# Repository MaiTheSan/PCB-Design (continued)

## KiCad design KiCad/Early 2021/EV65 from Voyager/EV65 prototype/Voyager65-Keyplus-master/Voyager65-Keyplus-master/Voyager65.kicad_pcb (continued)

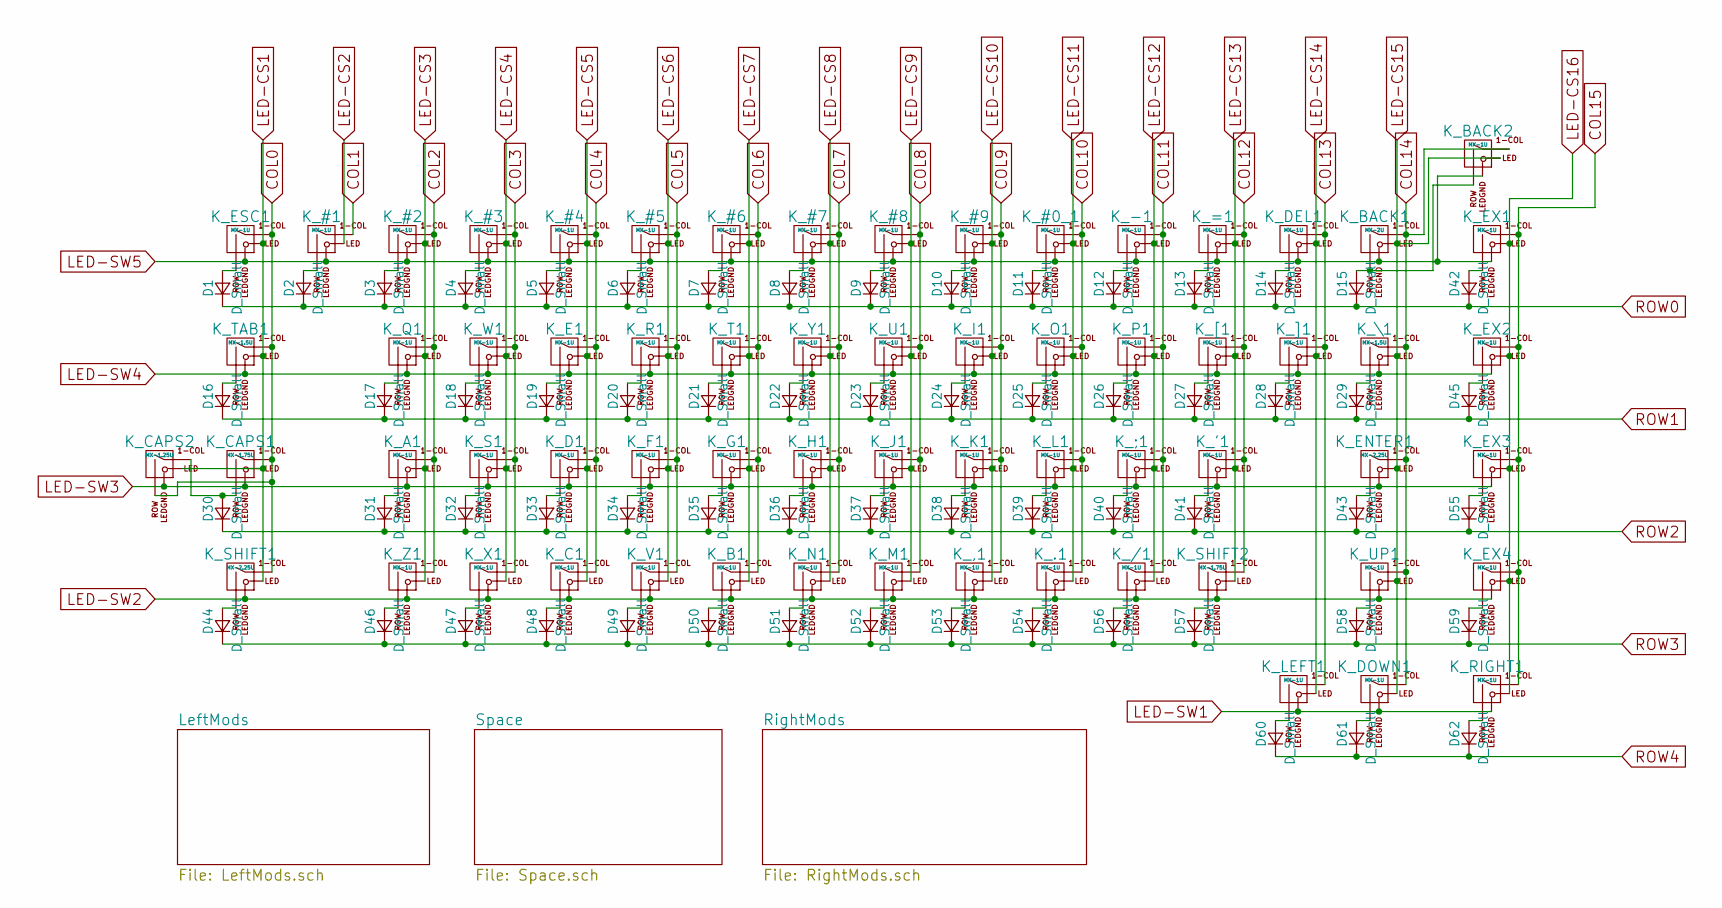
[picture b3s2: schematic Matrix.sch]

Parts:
D1, D2, D3, D4, D5, D6, D7, D8, D9, D10, D11, D12, D13, D14, D15, D16, D17, D18, D19, D20, D21, D22, D23, D24, D25, D26, D27, D28, D29, D30, D31, D32, D33, D34, D35, D36, D37, D38, D39, D40, D41, D42, D43, D44, D45, D46, D47, D48, D49, D50, D51, D52, D53, D54, D55, D56, D57, D58, D59, D60, D61, D62: D_Small; D_SOD-123
K_#0_1, K_#1, K_#2, K_#3, K_#4, K_#5, K_#6, K_#7, K_#8, K_#9: MX-1U; MXOnly-1U
K_'1: MX-1U; MXOnly-1U
K_,1: MX-1U; MXOnly-1U
K_-1: MX-1U; MXOnly-1U
K_.1: MX-1U; MXOnly-1U
K_/1: MX-1U; MXOnly-1U
K_;1: MX-1U; MXOnly-1U
K_=1: MX-1U; MXOnly-1U
K_A1: MX-1U; MXOnly-1U
K_B1: MX-1U; MXOnly-1U
K_BACK1: MX-2U; MXOnly-2U
K_BACK2: MX-1U; MXOnly-1U
K_C1: MX-1U; MXOnly-1U
K_CAPS1: MX-1.75U; MXOnly-1.75U
K_CAPS2: MX-1.25U; MXOnly-1.25U-FLIPPED
K_D1: MX-1U; MXOnly-1U
K_DEL1: MX-1U; MXOnly-1U
K_DOWN1: MX-1U; MXOnly-1U
K_E1: MX-1U; MXOnly-1U
K_ENTER1: MX-2.25U; MXOnly-2.25U
K_ESC1: MX-1U; MXOnly-1U
K_EX1, K_EX2, K_EX3, K_EX4: MX-1U; MXOnly-1U
K_F1: MX-1U; MXOnly-1U
K_G1: MX-1U; MXOnly-1U
K_H1: MX-1U; MXOnly-1U
K_I1: MX-1U; MXOnly-1U
K_J1: MX-1U; MXOnly-1U
K_K1: MX-1U; MXOnly-1U
K_L1: MX-1U; MXOnly-1U
K_LEFT1: MX-1U; MXOnly-1U
K_M1: MX-1U; MXOnly-1U
K_N1: MX-1U; MXOnly-1U
K_O1: MX-1U; MXOnly-1U
K_P1: MX-1U; MXOnly-1U
K_Q1: MX-1U; MXOnly-1U
K_R1: MX-1U; MXOnly-1U
K_RIGHT1: MX-1U; MXOnly-1U
K_S1: MX-1U; MXOnly-1U
K_SHIFT1: MX-2.25U; MXOnly-2.25U
K_SHIFT2: MX-1.75U; MXOnly-1.75U
K_T1: MX-1U; MXOnly-1U
K_TAB1: MX-1.5U; MXOnly-1.5U
K_U1: MX-1U; MXOnly-1U
K_UP1: MX-1U; MXOnly-1U
K_V1: MX-1U; MXOnly-1U
K_W1: MX-1U; MXOnly-1U
K_X1: MX-1U; MXOnly-1U
K_Y1: MX-1U; MXOnly-1U
K_Z1: MX-1U; MXOnly-1U
K_[1: MX-1U; MXOnly-1U
K_\1: MX-1.5U; MXOnly-1.5U
K_]1: MX-1U; MXOnly-1U

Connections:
COL0: K_CAPS1.1 (COL), K_CAPS2.2 (ROW), K_ESC1.1 (COL), K_SHIFT1.1 (COL), K_TAB1.1 (COL); also elsewhere on the board
COL1: K_#1.1 (COL); also elsewhere on the board
COL2: K_#2.1 (COL), K_A1.1 (COL), K_Q1.1 (COL), K_Z1.1 (COL); also elsewhere on the board
COL3: K_#3.1 (COL), K_S1.1 (COL), K_W1.1 (COL), K_X1.1 (COL); also elsewhere on the board
COL4: K_#4.1 (COL), K_C1.1 (COL), K_D1.1 (COL), K_E1.1 (COL); also elsewhere on the board
COL5: K_#5.1 (COL), K_F1.1 (COL), K_R1.1 (COL), K_V1.1 (COL); also elsewhere on the board
COL6: K_#6.1 (COL), K_B1.1 (COL), K_G1.1 (COL), K_T1.1 (COL); also elsewhere on the board
COL7: K_#7.1 (COL), K_H1.1 (COL), K_N1.1 (COL), K_Y1.1 (COL); also elsewhere on the board
COL8: K_#8.1 (COL), K_J1.1 (COL), K_M1.1 (COL), K_U1.1 (COL); also elsewhere on the board
COL9: K_#9.1 (COL), K_,1.1 (COL), K_I1.1 (COL), K_K1.1 (COL); also elsewhere on the board
COL10: K_#0_1.1 (COL), K_.1.1 (COL), K_L1.1 (COL), K_O1.1 (COL); also elsewhere on the board
COL11: K_-1.1 (COL), K_/1.1 (COL), K_;1.1 (COL), K_P1.1 (COL); also elsewhere on the board
COL12: K_'1.1 (COL), K_=1.1 (COL), K_SHIFT2.1 (COL), K_[1.1 (COL); also elsewhere on the board
COL13: K_DEL1.1 (COL), K_LEFT1.1 (COL), K_]1.1 (COL); also elsewhere on the board
COL14: K_BACK1.1 (COL), K_BACK2.1 (COL), K_DOWN1.1 (COL), K_ENTER1.1 (COL), K_UP1.1 (COL), K_\1.1 (COL); also elsewhere on the board
COL15: K_EX1.1 (COL), K_EX2.1 (COL), K_EX3.1 (COL), K_EX4.1 (COL), K_RIGHT1.1 (COL); also elsewhere on the board
LED-CS1: K_CAPS1.3 (LED), K_CAPS2.3 (LED), K_ESC1.3 (LED), K_SHIFT1.3 (LED), K_TAB1.3 (LED); also elsewhere on the board
LED-CS2: K_#1.3 (LED); also elsewhere on the board
LED-CS3: K_#2.3 (LED), K_A1.3 (LED), K_Q1.3 (LED), K_Z1.3 (LED); also elsewhere on the board
LED-CS4: K_#3.3 (LED), K_S1.3 (LED), K_W1.3 (LED), K_X1.3 (LED); also elsewhere on the board
LED-CS5: K_#4.3 (LED), K_C1.3 (LED), K_D1.3 (LED), K_E1.3 (LED); also elsewhere on the board
LED-CS6: K_#5.3 (LED), K_F1.3 (LED), K_R1.3 (LED), K_V1.3 (LED); also elsewhere on the board
LED-CS7: K_#6.3 (LED), K_B1.3 (LED), K_G1.3 (LED), K_T1.3 (LED); also elsewhere on the board
LED-CS8: K_#7.3 (LED), K_H1.3 (LED), K_N1.3 (LED), K_Y1.3 (LED); also elsewhere on the board
LED-CS9: K_#8.3 (LED), K_J1.3 (LED), K_M1.3 (LED), K_U1.3 (LED); also elsewhere on the board
LED-CS10: K_#9.3 (LED), K_,1.3 (LED), K_I1.3 (LED), K_K1.3 (LED); also elsewhere on the board
LED-CS11: K_#0_1.3 (LED), K_.1.3 (LED), K_L1.3 (LED), K_O1.3 (LED); also elsewhere on the board
LED-CS12: K_-1.3 (LED), K_/1.3 (LED), K_;1.3 (LED), K_P1.3 (LED); also elsewhere on the board
LED-CS13: K_'1.3 (LED), K_=1.3 (LED), K_SHIFT2.3 (LED), K_[1.3 (LED); also elsewhere on the board
LED-CS14: K_DEL1.3 (LED), K_LEFT1.3 (LED), K_]1.3 (LED); also elsewhere on the board
LED-CS15: K_BACK1.3 (LED), K_BACK2.3 (LED), K_DOWN1.3 (LED), K_ENTER1.3 (LED), K_UP1.3 (LED), K_\1.3 (LED); also elsewhere on the board
LED-CS16: K_EX1.3 (LED), K_EX2.3 (LED), K_EX3.3 (LED), K_EX4.3 (LED), K_RIGHT1.3 (LED); also elsewhere on the board
LED-SW1: K_DOWN1.4 (LEDGND), K_LEFT1.4 (LEDGND), K_RIGHT1.4 (LEDGND); also elsewhere on the board
LED-SW2: K_,1.4 (LEDGND), K_.1.4 (LEDGND), K_/1.4 (LEDGND), K_B1.4 (LEDGND), K_C1.4 (LEDGND), K_EX4.4 (LEDGND), K_M1.4 (LEDGND), K_N1.4 (LEDGND), K_SHIFT1.4 (LEDGND), K_SHIFT2.4 (LEDGND), K_UP1.4 (LEDGND), K_V1.4 (LEDGND), K_X1.4 (LEDGND), K_Z1.4 (LEDGND); also elsewhere on the board
LED-SW3: K_'1.4 (LEDGND), K_;1.4 (LEDGND), K_A1.4 (LEDGND), K_CAPS1.4 (LEDGND), K_CAPS2.4 (LEDGND), K_D1.4 (LEDGND), K_ENTER1.4 (LEDGND), K_EX3.4 (LEDGND), K_F1.4 (LEDGND), K_G1.4 (LEDGND), K_H1.4 (LEDGND), K_J1.4 (LEDGND), K_K1.4 (LEDGND), K_L1.4 (LEDGND), K_S1.4 (LEDGND); also elsewhere on the board
LED-SW4: K_E1.4 (LEDGND), K_EX2.4 (LEDGND), K_I1.4 (LEDGND), K_O1.4 (LEDGND), K_P1.4 (LEDGND), K_Q1.4 (LEDGND), K_R1.4 (LEDGND), K_T1.4 (LEDGND), K_TAB1.4 (LEDGND), K_U1.4 (LEDGND), K_W1.4 (LEDGND), K_Y1.4 (LEDGND), K_[1.4 (LEDGND), K_\1.4 (LEDGND), K_]1.4 (LEDGND); also elsewhere on the board
LED-SW5: K_#0_1.4 (LEDGND), K_#1.4 (LEDGND), K_#2.4 (LEDGND), K_#3.4 (LEDGND), K_#4.4 (LEDGND), K_#5.4 (LEDGND), K_#6.4 (LEDGND), K_#7.4 (LEDGND), K_#8.4 (LEDGND), K_#9.4 (LEDGND), K_-1.4 (LEDGND), K_=1.4 (LEDGND), K_BACK1.4 (LEDGND), K_BACK2.4 (LEDGND), K_DEL1.4 (LEDGND), K_ESC1.4 (LEDGND), K_EX1.4 (LEDGND); also elsewhere on the board
unnamed: D1.2 (A), K_ESC1.2 (ROW)
unnamed: D2.2 (A), K_#1.2 (ROW)
unnamed: D3.2 (A), K_#2.2 (ROW)
unnamed: D4.2 (A), K_#3.2 (ROW)
unnamed: D5.2 (A), K_#4.2 (ROW)
unnamed: D6.2 (A), K_#5.2 (ROW)
unnamed: D7.2 (A), K_#6.2 (ROW)
unnamed: D8.2 (A), K_#7.2 (ROW)
unnamed: D9.2 (A), K_#8.2 (ROW)
unnamed: D10.2 (A), K_#9.2 (ROW)
unnamed: D11.2 (A), K_#0_1.2 (ROW)
unnamed: D12.2 (A), K_-1.2 (ROW)
unnamed: D13.2 (A), K_=1.2 (ROW)
unnamed: D14.2 (A), K_DEL1.2 (ROW)
unnamed: D15.2 (A), K_BACK1.2 (ROW), K_BACK2.2 (ROW)
unnamed: D16.2 (A), K_TAB1.2 (ROW)
unnamed: D17.2 (A), K_Q1.2 (ROW)
unnamed: D18.2 (A), K_W1.2 (ROW)
unnamed: D19.2 (A), K_E1.2 (ROW)
unnamed: D20.2 (A), K_R1.2 (ROW)
unnamed: D21.2 (A), K_T1.2 (ROW)
unnamed: D22.2 (A), K_Y1.2 (ROW)
unnamed: D23.2 (A), K_U1.2 (ROW)
unnamed: D24.2 (A), K_I1.2 (ROW)
unnamed: D25.2 (A), K_O1.2 (ROW)
unnamed: D26.2 (A), K_P1.2 (ROW)
unnamed: D27.2 (A), K_[1.2 (ROW)
unnamed: D28.2 (A), K_]1.2 (ROW)
unnamed: D29.2 (A), K_\1.2 (ROW)
unnamed: D30.2 (A), K_CAPS1.2 (ROW), K_CAPS2.1 (COL)
unnamed: D31.2 (A), K_A1.2 (ROW)
unnamed: D32.2 (A), K_S1.2 (ROW)
unnamed: D33.2 (A), K_D1.2 (ROW)
unnamed: D34.2 (A), K_F1.2 (ROW)
unnamed: D35.2 (A), K_G1.2 (ROW)
unnamed: D36.2 (A), K_H1.2 (ROW)
unnamed: D37.2 (A), K_J1.2 (ROW)
unnamed: D38.2 (A), K_K1.2 (ROW)
unnamed: D39.2 (A), K_L1.2 (ROW)
unnamed: D40.2 (A), K_;1.2 (ROW)
unnamed: D41.2 (A), K_'1.2 (ROW)
unnamed: D42.2 (A), K_EX1.2 (ROW)
unnamed: D43.2 (A), K_ENTER1.2 (ROW)
unnamed: D44.2 (A), K_SHIFT1.2 (ROW)
unnamed: D45.2 (A), K_EX2.2 (ROW)
unnamed: D46.2 (A), K_Z1.2 (ROW)
unnamed: D47.2 (A), K_X1.2 (ROW)
unnamed: D48.2 (A), K_C1.2 (ROW)
unnamed: D49.2 (A), K_V1.2 (ROW)
unnamed: D50.2 (A), K_B1.2 (ROW)
unnamed: D51.2 (A), K_N1.2 (ROW)
unnamed: D52.2 (A), K_M1.2 (ROW)
unnamed: D53.2 (A), K_,1.2 (ROW)
unnamed: D54.2 (A), K_.1.2 (ROW)
unnamed: D55.2 (A), K_EX3.2 (ROW)
unnamed: D56.2 (A), K_/1.2 (ROW)
unnamed: D57.2 (A), K_SHIFT2.2 (ROW)
unnamed: D58.2 (A), K_UP1.2 (ROW)
unnamed: D59.2 (A), K_EX4.2 (ROW)
unnamed: D60.2 (A), K_LEFT1.2 (ROW)
unnamed: D61.2 (A), K_DOWN1.2 (ROW)
unnamed: D62.2 (A), K_RIGHT1.2 (ROW)
ROW0: D1.1 (K), D2.1 (K), D3.1 (K), D4.1 (K), D5.1 (K), D6.1 (K), D7.1 (K), D8.1 (K), D9.1 (K), D10.1 (K), D11.1 (K), D12.1 (K), D13.1 (K), D14.1 (K), D15.1 (K), D42.1 (K); also elsewhere on the board
ROW1: D16.1 (K), D17.1 (K), D18.1 (K), D19.1 (K), D20.1 (K), D21.1 (K), D22.1 (K), D23.1 (K), D24.1 (K), D25.1 (K), D26.1 (K), D27.1 (K), D28.1 (K), D29.1 (K), D45.1 (K); also elsewhere on the board
ROW2: D30.1 (K), D31.1 (K), D32.1 (K), D33.1 (K), D34.1 (K), D35.1 (K), D36.1 (K), D37.1 (K), D38.1 (K), D39.1 (K), D40.1 (K), D41.1 (K), D43.1 (K), D55.1 (K); also elsewhere on the board
ROW3: D44.1 (K), D46.1 (K), D47.1 (K), D48.1 (K), D49.1 (K), D50.1 (K), D51.1 (K), D52.1 (K), D53.1 (K), D54.1 (K), D56.1 (K), D57.1 (K), D58.1 (K), D59.1 (K); also elsewhere on the board
ROW4: D60.1 (K), D61.1 (K), D62.1 (K); also elsewhere on the board

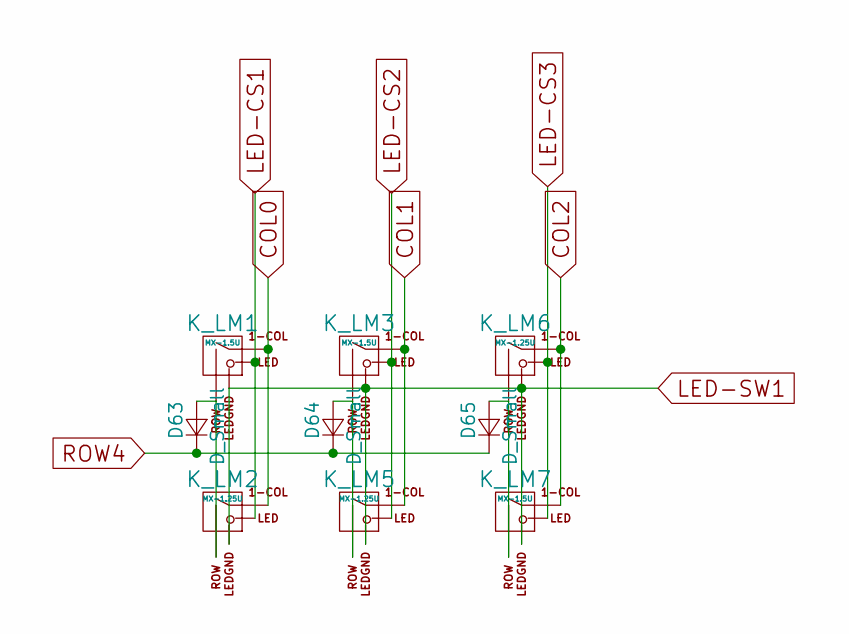
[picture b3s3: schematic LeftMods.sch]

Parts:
D63, D64, D65: D_Small; D_SOD-123
K_LM1, K_LM3, K_LM7: MX-1.5U; MXOnly-1.5U
K_LM2, K_LM5, K_LM6: MX-1.25U; MXOnly-1.25U-FLIPPED

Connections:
COL0: K_LM1.1 (COL), K_LM2.1 (COL); also elsewhere on the board
COL1: K_LM3.1 (COL), K_LM5.1 (COL); also elsewhere on the board
COL2: K_LM6.1 (COL), K_LM7.1 (COL); also elsewhere on the board
LED-CS1: K_LM1.3 (LED), K_LM2.3 (LED); also elsewhere on the board
LED-CS2: K_LM3.3 (LED), K_LM5.3 (LED); also elsewhere on the board
LED-CS3: K_LM6.3 (LED), K_LM7.3 (LED); also elsewhere on the board
LED-SW1: K_LM1.4 (LEDGND), K_LM2.4 (LEDGND), K_LM3.4 (LEDGND), K_LM5.4 (LEDGND), K_LM6.4 (LEDGND), K_LM7.4 (LEDGND); also elsewhere on the board
unnamed: D63.2 (A), K_LM1.2 (ROW), K_LM2.2 (ROW)
unnamed: D64.2 (A), K_LM3.2 (ROW), K_LM5.2 (ROW)
unnamed: D65.2 (A), K_LM6.2 (ROW), K_LM7.2 (ROW)
ROW4: D63.1 (K), D64.1 (K), D65.1 (K); also elsewhere on the board

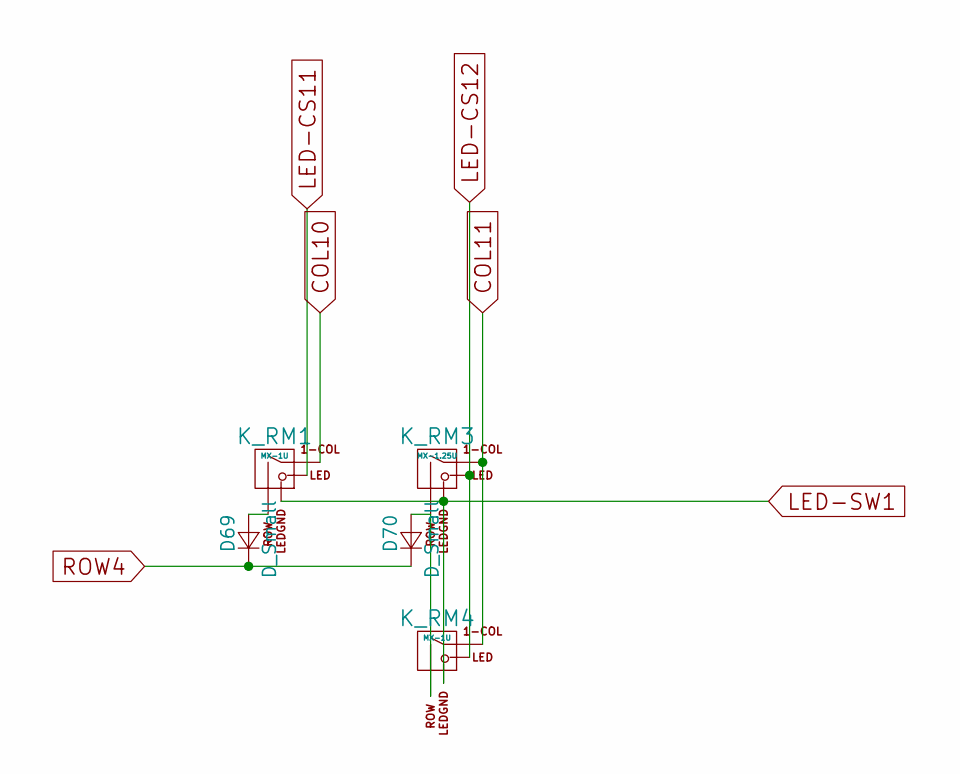
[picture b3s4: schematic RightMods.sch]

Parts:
D69, D70: D_Small; D_SOD-123
K_RM1: MX-1U; MXOnly-1.25U
K_RM3: MX-1.25U; MXOnly-1.25U
K_RM4: MX-1U; MXOnly-1.5U-FLIPPED

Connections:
COL10: K_RM1.1 (COL); also elsewhere on the board
COL11: K_RM3.1 (COL), K_RM4.1 (COL); also elsewhere on the board
LED-CS11: K_RM1.3 (LED); also elsewhere on the board
LED-CS12: K_RM3.3 (LED), K_RM4.3 (LED); also elsewhere on the board
LED-SW1: K_RM1.4 (LEDGND), K_RM3.4 (LEDGND), K_RM4.4 (LEDGND); also elsewhere on the board
unnamed: D69.2 (A), K_RM1.2 (ROW)
unnamed: D70.2 (A), K_RM3.2 (ROW), K_RM4.2 (ROW)
ROW4: D69.1 (K), D70.1 (K); also elsewhere on the board

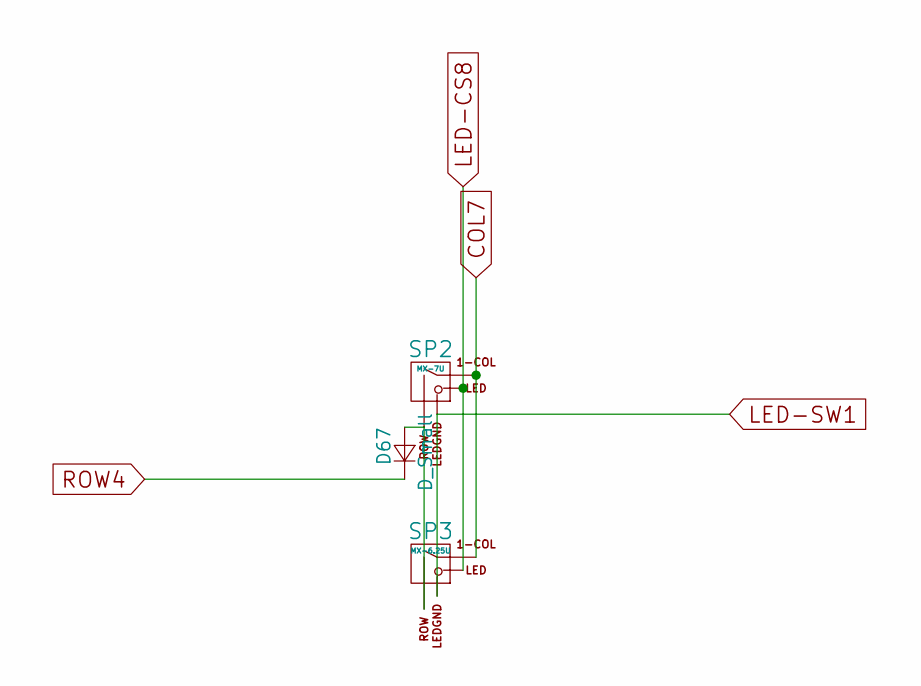
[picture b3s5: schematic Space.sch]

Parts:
D67: D_Small; D_SOD-123
SP2: MX-7U; MXOnly-7U-ReversedStabilizers
SP3: MX-6.25U; MXOnly-6.25U-ReversedStabilizers

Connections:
COL7: SP2.1 (COL), SP3.1 (COL); also elsewhere on the board
LED-CS8: SP2.3 (LED), SP3.3 (LED); also elsewhere on the board
LED-SW1: SP2.4 (LEDGND), SP3.4 (LEDGND); also elsewhere on the board
unnamed: D67.2 (A), SP2.2 (ROW), SP3.2 (ROW)
ROW4: D67.1 (K); also elsewhere on the board

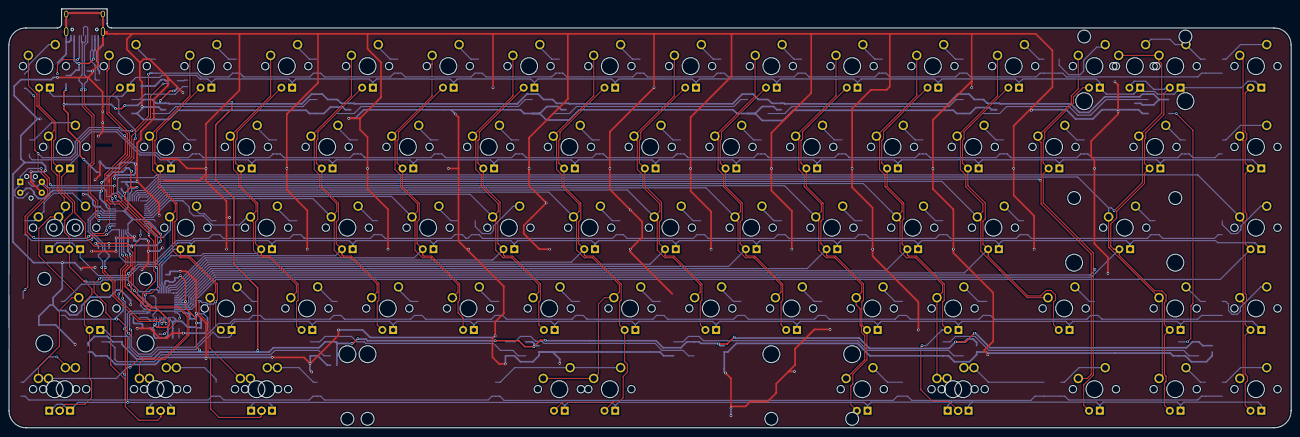
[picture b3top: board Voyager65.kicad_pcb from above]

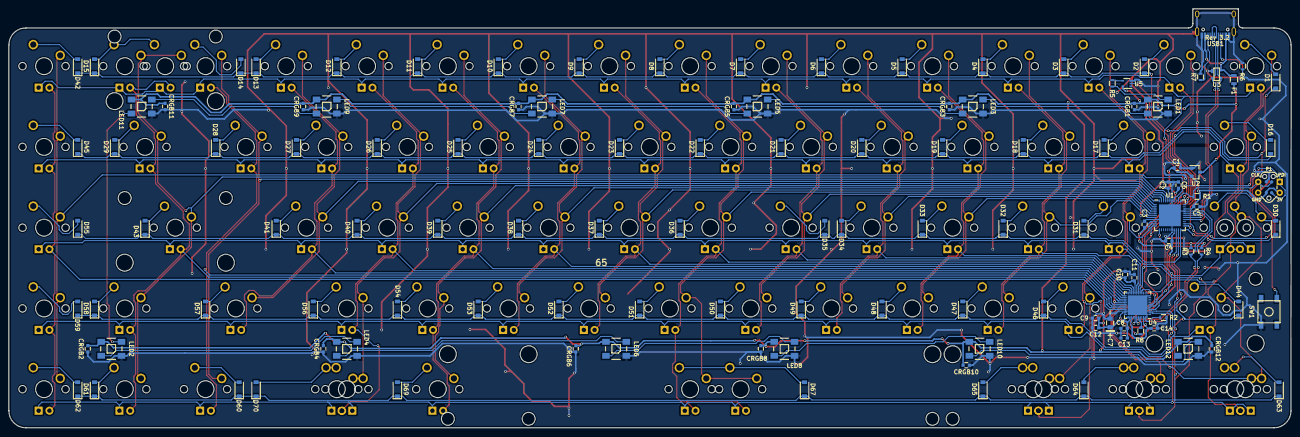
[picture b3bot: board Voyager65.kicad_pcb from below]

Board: 2 copper layers, 302.4 x 98.8 mm, 198 parts (123 on the bottom side), 139 nets.

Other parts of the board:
CRGB1, CRGB2, CRGB3, CRGB4, CRGB5, CRGB6, CRGB7, CRGB8, CRGB9, CRGB10, CRGB11, CRGB12: 0.1u; C_0603
LED1, LED2, LED3, LED4, LED5, LED6, LED7, LED8, LED9, LED10, LED11, LED12: WS2812B
R5: 470; R_0603
U5: 74LVC1G34; SOT-353_SC-70-5

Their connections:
+5V: CRGB1.1, CRGB2.1, CRGB3.1, CRGB4.1, CRGB5.1, CRGB6.1, CRGB7.1, CRGB8.1, CRGB9.1, CRGB10.1, CRGB11.1, CRGB12.1, LED1.1, LED2.1, LED3.1, LED4.1, LED5.1, LED6.1, LED7.1, LED8.1, LED9.1, LED10.1, LED11.1, LED12.1, U5.5; also elsewhere on the board
GND: CRGB1.2, CRGB2.2, CRGB3.2, CRGB4.2, CRGB5.2, CRGB6.2, CRGB7.2, CRGB8.2, CRGB9.2, CRGB10.2, CRGB11.2, CRGB12.2, LED1.3, LED2.3, LED3.3, LED4.3, LED5.3, LED6.3, LED7.3, LED8.3, LED9.3, LED10.3, LED11.3, LED12.3, U5.3; also elsewhere on the board
unnamed: LED1.2, LED3.4
unnamed: LED1.4, R5.2
unnamed: LED2.2, LED4.4
unnamed: LED3.2, LED5.4
unnamed: LED4.2, LED6.4
unnamed: LED5.2, LED7.4
unnamed: LED6.2, LED8.4
unnamed: LED7.2, LED9.4
unnamed: LED10.2, LED12.4
unnamed: LED8.2, LED10.4
unnamed: LED2.4, LED11.2
unnamed: LED9.2, LED11.4
unnamed: R5.1, U5.4
RGBLED: U5.2; also elsewhere on the board

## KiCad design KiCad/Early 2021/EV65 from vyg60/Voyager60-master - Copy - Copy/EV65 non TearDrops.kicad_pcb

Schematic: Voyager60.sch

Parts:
C2: 10uF; C_0603
C3, C4, C5: 0.1uF; C_0603
C6: 1uF; C_0603
C7, C8: 22pF; C_0603
D1, D2, D3, D4, D5, D6, D7, D8, D9, D10, D11, D12, D13, D14, D15, D16, D17, D18, D19, D20, D21, D22, D23, D24, D25, D26, D27, D28, D29, D30, D31, D32, D33, D34, D35, D36, D37, D38, D39, D40, D41, D42, D43, D45, D46, D47, D48, D49, D50, D51, D52, D53, D54, D55, D56, D57, D58, D59, D60, D61, D62, D63, D64, D65, D66, D67, D69: SOD-123; D_SOD-123
D44: LED; LED_D3.0mm
F1: 500mA; Fuse_SMD1206_Reflow
K_#1, K_#2, K_#3, K_#4, K_#5, K_#6, K_#7, K_#8, K_#9, K_#10: MX-1U; MXOnly-1U
K_'1: MX-1U; MXOnly-1U
K_,1: MX-1U; MXOnly-1U
K_-1: MX-1U; MXOnly-1U
K_.1: MX-1U; MXOnly-1U
K_/1: MX-1U; MXOnly-1U
K_;1: MX-1U; MXOnly-1U
K_=1: MX-1U; MXOnly-1U
K_A1: MX-1U; MXOnly-1U
K_ALT1: MX-1.25U; MXOnly-1.25U
K_ALT2: MX-1.5U; MXOnly-1.5U-FLIPPED
K_B1: MX-1U; MXOnly-1U
K_BACK1: MX-2U; MXOnly-2U
K_C1: MX-1U; MXOnly-1U
K_CAPS1: MX-1.75U; MXOnly-1.75U
K_CAPS2: MX-1.25U; MXOnly-1.25U-FLIPPED
K_CTRL1: MX-1.25U; MXOnly-1.25U
K_CTRL2: MX-1.5U; MXOnly-1.5U-FLIPPED
K_D1: MX-1U; MXOnly-1U
K_E1: MX-1U; MXOnly-1U
K_ENTER1: MX-2.25U; MXOnly-2.25U
K_ESC1: MX-1U; MXOnly-1U
K_F1: MX-1U; MXOnly-1U
K_FNC1, K_FNC2, K_FNC3, K_FNC4, K_FNC5: MX-1U; MXOnly-1U-FLIPPED
K_G1: MX-1U; MXOnly-1U
K_H1: MX-1U; MXOnly-1U
K_I1: MX-1U; MXOnly-1U
K_J1: MX-1U; MXOnly-1U
K_K1: MX-1U; MXOnly-1U
K_L1: MX-1U; MXOnly-1U
K_M1: MX-1U; MXOnly-1U
K_N1: MX-1U; MXOnly-1U
K_O1: MX-1U; MXOnly-1U
K_P1: MX-1U; MXOnly-1U
K_Q1: MX-1U; MXOnly-1U
K_R1: MX-1U; MXOnly-1U
K_RALT2: MX-1.25U; MXOnly-1.25U-FLIPPED
K_RALT3: MX-1.5U; MXOnly-1.5U-FLIPPED
K_RCTRL2: MX-1U; MXOnly-1U
K_RMENU2: MX-1U; MXOnly-1U
K_RWIN2: MX-1.25U; MXOnly-1.25U
K_S1: MX-1U; MXOnly-1U
K_SHIFT1: MX-2.25U; MXOnly-2.25U
K_SPACE1: MX-7U; MXOnly-7U-ReversedStabilizers
K_SPACE2: MX-6.25U; MXOnly-6.25U-ReversedStabilizers
K_SRSHIFT1: MX-1.75U; MXOnly-1.75U
K_SRSHIFT2: MX-1U; MXOnly-1U
K_T1: MX-1U; MXOnly-1U
K_TAB1: MX-1.5U; MXOnly-1.5U
K_U1: MX-1U; MXOnly-1U
K_V1: MX-1U; MXOnly-1U
K_W1: MX-1U; MXOnly-1U
K_WIN1: MX-1.25U; MXOnly-1.25U
K_WIN2: MX-1U; MXOnly-1U-FLIPPED
K_X1: MX-1U; MXOnly-1U
K_Y1: MX-1U; MXOnly-1U
K_Z1: MX-1U; MXOnly-1U
K_[1: MX-1U; MXOnly-1U
K_\1: MX-1.5U; MXOnly-1.5U
K_]1: MX-1U; MXOnly-1U
Q1: 2N7002; SOT-23
R1, R2, R3, R4, R5, R6, R7, R8, R9, R10, R11, R12, R13, R14, R15, R16, R17, R18, R19, R20, R21, R22, R23, R24, R25, R26, R27, R28, R29, R30, R32, R33, R34, R35, R36, R37, R38, R39, R40, R41, R42, R43, R45, R46, R47, R48, R49, R50, R51, R52, R53, R54, R55, R56, R57, R58, R59, R60, R61, R62, R63, R64, R65, R66, R69, R71, R72, R75, R76: 1k; R_0805
R31: 300; R_0805
R44: 500; R_0805
R67, R68: 22; R_0805
R70: 10k; R_0805
R73, R74: 5.1k; R_0805
RGB1, RGB2, RGB3, RGB4, RGB5, RGB6, RGB7, RGB8, RGB9, RGB10, RGB11, RGB12, RGB13, RGB14: WS2812B
SW1: 5.2x5.2mm; SKQG-1155865
U1: ATmega32U4-MU; QFN-44-1EP_7x7mm_Pitch0.5mm
U2: PRTR5V0U2X; SOT143B
U3: STF202-22T1G; Reset_Pretty
USB1: HRO-TYPE-C-31-M-12; HRO-TYPE-C-31-M-12-Assembly
Y1: 16Mhz; Crystal_SMD_3225-4Pin_3.2x2.5mm

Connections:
+5V: C2.2, C3.2, C4.2, C5.2, F1.1, K_#1.3 (LED), K_#2.3 (LED), K_#3.3 (LED), K_#4.3 (LED), K_#5.3 (LED), K_#6.3 (LED), K_#7.3 (LED), K_#8.3 (LED), K_#9.3 (LED), K_#10.3 (LED), K_'1.3 (LED), K_,1.3 (LED), K_-1.3 (LED), K_.1.3 (LED), K_/1.3 (LED), K_;1.3 (LED), K_=1.3 (LED), K_A1.3 (LED), K_ALT1.3 (LED), K_ALT2.3 (LED), K_B1.3 (LED), K_BACK1.3 (LED), K_C1.3 (LED), K_CAPS1.3 (LED), K_CAPS2.3 (LED), K_CTRL1.3 (LED), K_CTRL2.3 (LED), K_D1.3 (LED), K_E1.3 (LED), K_ENTER1.3 (LED), K_ESC1.3 (LED), K_F1.3 (LED), K_FNC1.3 (LED), K_FNC2.3 (LED), K_FNC3.3 (LED), K_FNC4.3 (LED), K_FNC5.3 (LED), K_G1.3 (LED), K_H1.3 (LED), K_I1.3 (LED), K_J1.3 (LED), K_K1.3 (LED), K_L1.3 (LED), K_M1.3 (LED), K_N1.3 (LED), K_O1.3 (LED), K_P1.3 (LED), K_Q1.3 (LED), K_R1.3 (LED), K_RALT2.3 (LED), K_RALT3.3 (LED), K_RCTRL2.3 (LED), K_RMENU2.3 (LED), K_RWIN2.3 (LED), K_S1.3 (LED), K_SHIFT1.3 (LED), K_SPACE1.3 (LED), K_SPACE2.3 (LED), K_SRSHIFT1.3 (LED), K_SRSHIFT2.3 (LED), K_T1.3 (LED), K_TAB1.3 (LED), K_U1.3 (LED), K_V1.3 (LED), K_W1.3 (LED), K_WIN1.3 (LED), K_WIN2.3 (LED), K_X1.3 (LED), K_Y1.3 (LED), K_Z1.3 (LED), K_[1.3 (LED), K_\1.3 (LED), K_]1.3 (LED), R70.1, RGB1.1 (VCC), RGB2.1 (VCC), RGB3.1 (VCC), RGB4.1 (VCC), RGB5.1 (VCC), RGB6.1 (VCC), RGB7.1 (VCC), RGB8.1 (VCC), RGB9.1 (VCC), RGB10.1 (VCC), RGB11.1 (VCC), RGB12.1 (VCC), RGB13.1 (VCC), RGB14.1 (VCC), U1.2 (UVCC), U1.7 (VBUS), U1.14 (VCC), U1.24 (AVCC), U1.34 (VCC), U1.44 (AVCC), U3.2 (DIN1); also elsewhere on the board
COL0: K_CAPS1.1 (COL), K_CAPS2.2 (ROW), K_CTRL1.1 (COL), K_CTRL2.1 (COL), K_ESC1.1 (COL), K_SHIFT1.1 (COL), K_TAB1.1 (COL), U1.39 (PF4)
COL1: K_#1.1 (COL), K_A1.1 (COL), K_Q1.1 (COL), K_WIN1.1 (COL), K_WIN2.1 (COL), U1.36 (PF7)
COL2: K_#2.1 (COL), K_ALT1.1 (COL), K_ALT2.1 (COL), K_S1.1 (COL), K_W1.1 (COL), K_Z1.1 (COL), U1.38 (PF5)
COL3: K_#3.1 (COL), K_D1.1 (COL), K_E1.1 (COL), K_X1.1 (COL), U1.37 (PF6)
COL4: K_#4.1 (COL), K_C1.1 (COL), K_F1.1 (COL), K_R1.1 (COL), U1.32 (PC7)
COL5: K_#5.1 (COL), K_G1.1 (COL), K_T1.1 (COL), K_V1.1 (COL), U1.31 (PC6)
COL6: K_#6.1 (COL), K_B1.1 (COL), K_H1.1 (COL), K_SPACE1.1 (COL), K_SPACE2.1 (COL), K_Y1.1 (COL), U1.30 (PB6)
COL7: K_#7.1 (COL), K_J1.1 (COL), K_N1.1 (COL), K_U1.1 (COL), U1.29 (PB5)
COL8: K_#8.1 (COL), K_I1.1 (COL), K_K1.1 (COL), K_M1.1 (COL), U1.28 (PB4)
COL9: K_#9.1 (COL), K_,1.1 (COL), K_L1.1 (COL), K_O1.1 (COL), U1.27 (PD7)
COL10: K_#10.1 (COL), K_.1.1 (COL), K_;1.1 (COL), K_P1.1 (COL), K_RALT2.1 (COL), U1.26 (PD6)
COL11: K_'1.1 (COL), K_-1.1 (COL), K_/1.1 (COL), K_RALT3.1 (COL), K_RWIN2.1 (COL), K_[1.1 (COL), U1.25 (PD4)
COL12: K_=1.1 (COL), K_RMENU2.1 (COL), K_SRSHIFT1.1 (COL), K_]1.1 (COL), U1.22 (PD5)
COL13: K_BACK1.1 (COL), K_ENTER1.1 (COL), K_RCTRL2.1 (COL), K_SRSHIFT2.1 (COL), K_\1.1 (COL), U1.21 (PD3)
COL14: K_FNC1.1 (COL), K_FNC2.1 (COL), K_FNC3.1 (COL), K_FNC4.1 (COL), K_FNC5.1 (COL), U1.20 (PD2)
D+: R68.1, U1.4 (D+)
D-: R67.1, U1.3 (D-)
GND: C2.1, C3.1, C4.1, C5.1, C6.2, C7.2, C8.2, Q1.2 (S), R71.1, R73.1, R74.1, RGB1.3 (GND), RGB2.3 (GND), RGB3.3 (GND), RGB4.3 (GND), RGB5.3 (GND), RGB6.3 (GND), RGB7.3 (GND), RGB8.3 (GND), RGB9.3 (GND), RGB10.3 (GND), RGB11.3 (GND), RGB12.3 (GND), RGB13.3 (GND), RGB14.3 (GND), SW1.1, U1.5 (UGND), U1.15 (GND), U1.23 (GND), U1.35 (GND), U1.43 (GND), U1.45 (GND), U2.1 (GND), U3.6 (GND), USB1.1 (GND), USB1.12 (GND), USB1.13 (SHIELD), Y1.2, Y1.4; also elsewhere on the board
unnamed: C6.1, U1.6 (UCAP)
unnamed: C7.1, U1.17 (XTAL1), Y1.1
unnamed: C8.1, U1.16 (XTAL2), Y1.3
unnamed: D1.2 (A), K_ESC1.2 (ROW)
unnamed: D2.2 (A), K_#1.2 (ROW)
unnamed: D3.2 (A), K_#2.2 (ROW)
unnamed: D4.2 (A), K_#3.2 (ROW)
unnamed: D5.2 (A), K_#4.2 (ROW)
unnamed: D6.2 (A), K_#5.2 (ROW)
unnamed: D7.2 (A), K_#6.2 (ROW)
unnamed: D8.2 (A), K_#7.2 (ROW)
unnamed: D9.2 (A), K_#8.2 (ROW)
unnamed: D10.2 (A), K_#9.2 (ROW)
unnamed: D11.2 (A), K_#10.2 (ROW)
unnamed: D12.2 (A), K_-1.2 (ROW)
unnamed: D13.2 (A), K_=1.2 (ROW)
unnamed: D14.2 (A), K_BACK1.2 (ROW)
unnamed: D15.2 (A), K_FNC1.2 (ROW)
unnamed: D16.2 (A), K_TAB1.2 (ROW)
unnamed: D17.2 (A), K_Q1.2 (ROW)
unnamed: D18.2 (A), K_W1.2 (ROW)
unnamed: D19.2 (A), K_E1.2 (ROW)
unnamed: D20.2 (A), K_R1.2 (ROW)
unnamed: D21.2 (A), K_T1.2 (ROW)
unnamed: D22.2 (A), K_Y1.2 (ROW)
unnamed: D23.2 (A), K_U1.2 (ROW)
unnamed: D24.2 (A), K_I1.2 (ROW)
unnamed: D25.2 (A), K_O1.2 (ROW)
unnamed: D26.2 (A), K_P1.2 (ROW)
unnamed: D27.2 (A), K_[1.2 (ROW)
unnamed: D28.2 (A), K_]1.2 (ROW)
unnamed: D29.2 (A), K_\1.2 (ROW)
unnamed: D30.2 (A), K_RMENU2.2 (ROW)
unnamed: D31.2 (A), K_CAPS1.2 (ROW), K_CAPS2.1 (COL)
unnamed: D32.2 (A), K_A1.2 (ROW)
unnamed: D33.2 (A), K_S1.2 (ROW)
unnamed: D34.2 (A), K_D1.2 (ROW)
unnamed: D35.2 (A), K_F1.2 (ROW)
unnamed: D36.2 (A), K_G1.2 (ROW)
unnamed: D37.2 (A), K_H1.2 (ROW)
unnamed: D38.2 (A), K_J1.2 (ROW)
unnamed: D39.2 (A), K_K1.2 (ROW)
unnamed: D40.2 (A), K_L1.2 (ROW)
unnamed: D41.2 (A), K_;1.2 (ROW)
unnamed: D42.2 (A), K_'1.2 (ROW)
unnamed: D43.2 (A), K_ENTER1.2 (ROW)
unnamed: D45.2 (A), K_SHIFT1.2 (ROW)
unnamed: D46.2 (A), K_Z1.2 (ROW)
unnamed: D47.2 (A), K_X1.2 (ROW)
unnamed: D48.2 (A), K_C1.2 (ROW)
unnamed: D49.2 (A), K_V1.2 (ROW)
unnamed: D50.2 (A), K_B1.2 (ROW)
unnamed: D51.2 (A), K_N1.2 (ROW)
unnamed: D52.2 (A), K_M1.2 (ROW)
unnamed: D53.2 (A), K_,1.2 (ROW)
unnamed: D54.2 (A), K_.1.2 (ROW)
unnamed: D55.2 (A), K_/1.2 (ROW)
unnamed: D56.2 (A), K_SRSHIFT1.2 (ROW)
unnamed: D57.2 (A), K_SRSHIFT2.2 (ROW)
unnamed: D58.2 (A), K_FNC2.2 (ROW)
unnamed: D59.2 (A), K_CTRL1.2 (ROW), K_CTRL2.2 (ROW)
unnamed: D60.2 (A), K_WIN1.2 (ROW), K_WIN2.2 (ROW)
unnamed: D61.2 (A), K_SPACE1.2 (ROW), K_SPACE2.2 (ROW)
unnamed: D62.2 (A), K_FNC3.2 (ROW)
unnamed: D63.2 (A), K_RALT2.2 (ROW)
unnamed: D64.2 (A), K_RALT3.2 (ROW), K_RWIN2.2 (ROW)
unnamed: D65.2 (A), K_RCTRL2.2 (ROW)
unnamed: D66.2 (A), K_FNC4.2 (ROW)
unnamed: D67.2 (A), K_ALT1.2 (ROW), K_ALT2.2 (ROW)
unnamed: D69.2 (A), K_FNC5.2 (ROW)
unnamed: K_#1.4 (LEDGND), R2.1
unnamed: K_#2.4 (LEDGND), R3.1
unnamed: K_#3.4 (LEDGND), R4.1
unnamed: K_#4.4 (LEDGND), R5.1
unnamed: K_#5.4 (LEDGND), R6.1
unnamed: K_#6.4 (LEDGND), R7.1
unnamed: K_#7.4 (LEDGND), R8.1
unnamed: K_#8.4 (LEDGND), R9.1
unnamed: K_#9.4 (LEDGND), R10.1
unnamed: K_#10.4 (LEDGND), R11.1
unnamed: K_'1.4 (LEDGND), R42.1
unnamed: K_,1.4 (LEDGND), R53.1
unnamed: K_-1.4 (LEDGND), R12.1
unnamed: K_.1.4 (LEDGND), R54.1
unnamed: K_/1.4 (LEDGND), R55.1
unnamed: K_;1.4 (LEDGND), R41.1
unnamed: K_=1.4 (LEDGND), R13.1
unnamed: K_A1.4 (LEDGND), R32.1
unnamed: K_ALT1.4 (LEDGND), K_ALT2.4 (LEDGND), R72.1
unnamed: K_B1.4 (LEDGND), R50.1
unnamed: K_BACK1.4 (LEDGND), R14.1
unnamed: K_C1.4 (LEDGND), R48.1
unnamed: K_CAPS1.4 (LEDGND), K_CAPS2.4 (LEDGND), R31.1
unnamed: K_CTRL1.4 (LEDGND), K_CTRL2.4 (LEDGND), R59.1
unnamed: K_D1.4 (LEDGND), R34.1
unnamed: K_E1.4 (LEDGND), R19.1
unnamed: K_ENTER1.4 (LEDGND), R43.1
unnamed: K_ESC1.4 (LEDGND), R1.1
unnamed: K_F1.4 (LEDGND), R35.1
unnamed: K_FNC1.4 (LEDGND), R15.1
unnamed: K_FNC2.4 (LEDGND), R58.1
unnamed: K_FNC3.4 (LEDGND), R62.1
unnamed: K_FNC4.4 (LEDGND), R66.1
unnamed: K_FNC5.4 (LEDGND), R76.1
unnamed: K_G1.4 (LEDGND), R36.1
unnamed: K_H1.4 (LEDGND), R37.1
unnamed: K_I1.4 (LEDGND), R24.1
unnamed: K_J1.4 (LEDGND), R38.1
unnamed: K_K1.4 (LEDGND), R39.1
unnamed: K_L1.4 (LEDGND), R40.1
unnamed: K_M1.4 (LEDGND), R52.1
unnamed: K_N1.4 (LEDGND), R51.1
unnamed: K_O1.4 (LEDGND), R25.1
unnamed: K_P1.4 (LEDGND), R26.1
unnamed: K_Q1.4 (LEDGND), R17.1
unnamed: K_R1.4 (LEDGND), R20.1
unnamed: K_RALT2.4 (LEDGND), R63.1
unnamed: K_RALT3.4 (LEDGND), K_RWIN2.4 (LEDGND), R64.1
unnamed: K_RCTRL2.4 (LEDGND), R65.1
unnamed: K_RMENU2.4 (LEDGND), R30.1
unnamed: K_S1.4 (LEDGND), R33.1
unnamed: K_SHIFT1.4 (LEDGND), R45.1
unnamed: K_SPACE1.4 (LEDGND), K_SPACE2.4 (LEDGND), R61.1
unnamed: K_SRSHIFT1.4 (LEDGND), R56.1
unnamed: K_SRSHIFT2.4 (LEDGND), R57.1
unnamed: K_T1.4 (LEDGND), R21.1
unnamed: K_TAB1.4 (LEDGND), R16.1
unnamed: K_U1.4 (LEDGND), R23.1
unnamed: K_V1.4 (LEDGND), R49.1
unnamed: K_W1.4 (LEDGND), R18.1
unnamed: K_WIN1.4 (LEDGND), K_WIN2.4 (LEDGND), R60.1
unnamed: K_X1.4 (LEDGND), R47.1
unnamed: K_Y1.4 (LEDGND), R22.1
unnamed: K_Z1.4 (LEDGND), R46.1
unnamed: K_[1.4 (LEDGND), R27.1
unnamed: K_\1.4 (LEDGND), R29.1
unnamed: K_]1.4 (LEDGND), R28.1
unnamed: Q1.1 (G), R69.1
unnamed: R67.2, U2.3 (IO2), USB1.5 (DN2), USB1.7 (DN1)
unnamed: R68.2, U2.2 (IO1), USB1.6 (DP1), USB1.8 (DP2)
unnamed: R69.2, U1.12 (PB7)
unnamed: R70.2, SW1.2, U1.13 (~RESET), U3.5 (DOUT1)
unnamed: R71.2, U1.33 (~HWB~/PE2)
unnamed: R73.2, USB1.4 (CC1)
unnamed: R74.2, USB1.10 (CC2)
unnamed: RGB1.2 (DOUT), RGB3.4 (DIN)
unnamed: RGB2.2 (DOUT), RGB4.4 (DIN)
unnamed: RGB3.2 (DOUT), RGB5.4 (DIN)
unnamed: RGB4.2 (DOUT), RGB6.4 (DIN)
unnamed: RGB5.2 (DOUT), RGB7.4 (DIN)
unnamed: RGB6.2 (DOUT), RGB8.4 (DIN)
unnamed: RGB7.2 (DOUT), RGB9.4 (DIN)
unnamed: RGB10.2 (DOUT), RGB12.4 (DIN)
unnamed: RGB8.2 (DOUT), RGB10.4 (DIN)
unnamed: RGB11.2 (DOUT), RGB13.4 (DIN)
unnamed: RGB9.2 (DOUT), RGB11.4 (DIN)
unnamed: RGB12.2 (DOUT), RGB14.4 (DIN)
unnamed: RGB2.4 (DIN), RGB13.2 (DOUT)
RGBLED: R44.1, R44.2, RGB1.4 (DIN), U1.19 (PD1)
ROW0: D1.1 (K), D2.1 (K), D3.1 (K), D4.1 (K), D5.1 (K), D6.1 (K), D7.1 (K), D8.1 (K), D9.1 (K), D10.1 (K), D11.1 (K), D12.1 (K), D13.1 (K), D14.1 (K), D15.1 (K), U1.9 (PB1), U3.3 (DIN2)
ROW1: D16.1 (K), D17.1 (K), D18.1 (K), D19.1 (K), D20.1 (K), D21.1 (K), D22.1 (K), D23.1 (K), D24.1 (K), D25.1 (K), D26.1 (K), D27.1 (K), D28.1 (K), D29.1 (K), D58.1 (K), U1.10 (PB2), U3.4 (DOUT2)
ROW2: D31.1 (K), D32.1 (K), D33.1 (K), D34.1 (K), D35.1 (K), D36.1 (K), D37.1 (K), D38.1 (K), D39.1 (K), D40.1 (K), D41.1 (K), D42.1 (K), D43.1 (K), D62.1 (K), U1.11 (PB3), U3.1 (VBUS)
ROW3: D45.1 (K), D46.1 (K), D47.1 (K), D48.1 (K), D49.1 (K), D50.1 (K), D51.1 (K), D52.1 (K), D53.1 (K), D54.1 (K), D55.1 (K), D56.1 (K), D57.1 (K), D66.1 (K), U1.41 (PF0)
ROW4: D30.1 (K), D59.1 (K), D60.1 (K), D61.1 (K), D63.1 (K), D64.1 (K), D65.1 (K), D67.1 (K), D69.1 (K), U1.40 (PF1)
VCC: F1.2, U2.4 (VCC), USB1.2 (VBUS), USB1.11 (VBUS)

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
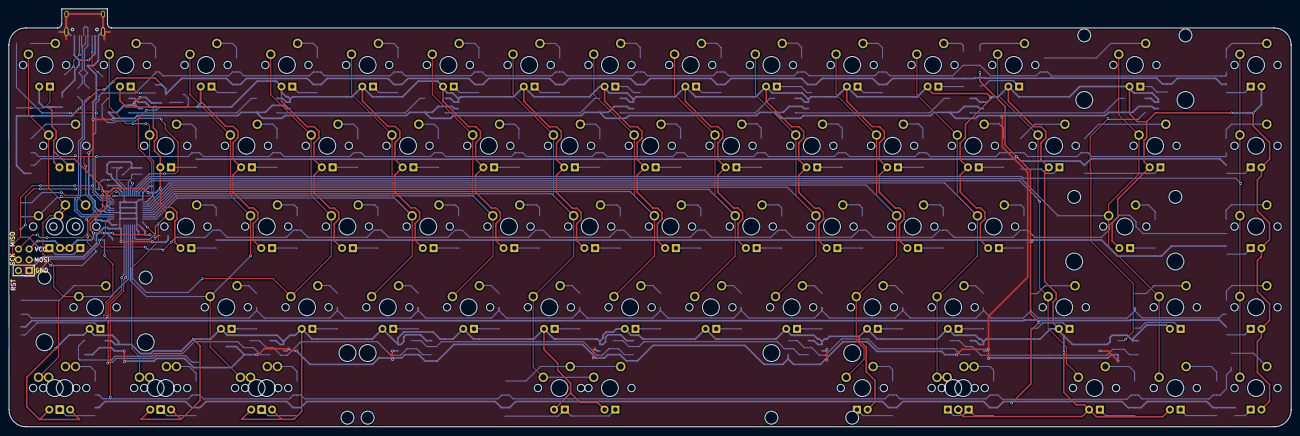
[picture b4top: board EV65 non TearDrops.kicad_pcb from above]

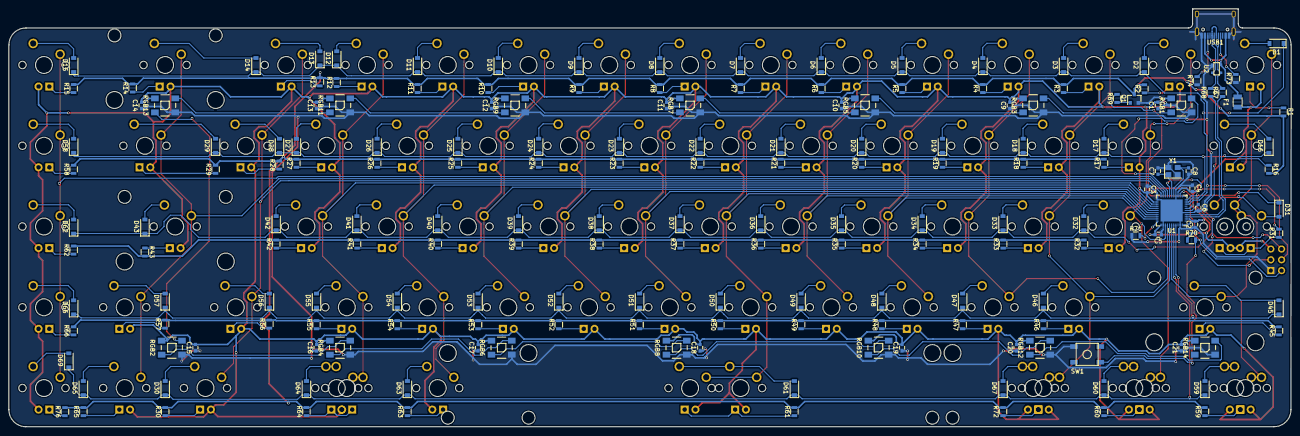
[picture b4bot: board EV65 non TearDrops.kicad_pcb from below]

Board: 2 copper layers, 302.4 x 98.5 mm, 257 parts (183 on the bottom side), 186 nets.

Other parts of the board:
C1, C9, C10, C11, C12, C13, C14, C15, C16, C17, C18, C19, C20, C21: 0.1uF; C_0603

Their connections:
+5V: C1.2, C9.2, C10.2, C11.2, C12.2, C13.2, C14.2, C15.2, C16.2, C17.2, C18.2, C19.2, C20.2, C21.2; also elsewhere on the board
GND: C1.1, C9.1, C10.1, C11.1, C12.1, C13.1, C14.1, C15.1, C16.1, C17.1, C18.1, C19.1, C20.1, C21.1; also elsewhere on the board

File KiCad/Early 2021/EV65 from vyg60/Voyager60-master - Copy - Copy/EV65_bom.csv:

Component,Description,Part,References,Value,Footprint,Quantity Per PCB,Datasheet
1,"Capacitor, Ceramic, 15V or more",C_Small,C1 C3 C4 C5 C9 C10 C11 C12 C13 C14 C15 C16 C17 C18 C19 C20 C21,0.1uF,C_0603,17,
2,"Capacitor, Ceramic, 15V or more",C_Small,C2,10uF,C_0603,1,
3,"Capacitor, Ceramic, 15V or more",C_Small,C6,1uF,C_0603,1,
4,"Capacitor, Ceramic, 15V or more",C_Small,C7 C8,22pF,C_0603,2,
5,"Diode, Generic",D_Small,D1 D2 D3 D4 D5 D6 D7 D8 D9 D10 D11 D12 D13 D14 D16 D17 D18 D19 D20 D21 D22 D23 D24 D25 D26 D27 D28 D29 D30 D31 D32 D33 D34 D35 D36 D37 D38 D39 D40 D41 D42 D43 D45 D46 D47 D48 D49 D50 D51 D52 D53 D54 D55 D56 D57 D58 D59 D60 D61 D62 D63 D64 D65 D67 D69,SOD-123,D_SOD-123,66,
6,"Polyfuse, 500mA hold, 1A trip",Polyfuse_Small,F1,500mA,Fuse_SMD1206_Reflow,1,
7,N-Channel MOSFET,2N7002,Q1,2N7002,SOT-23,1,https://www.fairchildsemi.com/datasheets/2N/2N7002.pdf
8,"Resistor, Generic",R_Small,R70,10k,R_0805,1,
9,"resistor, Generic",R_Small,R31,300,R_0805,1,
10,"Resistor, Generic",R_Small,R1 R2 R3 R4 R5 R6 R7 R8 R9 R10 R11 R12 R13 R14 R16 R17 R18 R19 R20 R21 R22 R23 R24 R25 R26 R27 R28 R29 R30 R32 R33 R34 R35 R36 R37 R38 R39 R40 R41 R42 R43 R45 R46 R47 R48 R49 R50 R51 R52 R53 R54 R55 R56 R57 R58 R59 R60 R61 R62 R63 R64 R65 R66 R69 R71 R72 R76,1k,R_0805,69,
11,"Resistor, Generic",R_Small,R67 R68,22,R_0805,2,
12,"Resistor, Generic",R_Small,R73 R74,5.1k,R_0805,2,
13,"WS2812B RGB LED, 5050",WS2812B,RGB1 RGB2 RGB3 RGB4 RGB5 RGB6 RGB7 RGB8 RGB9 RGB10 RGB11 RGB12 RGB13 RGB14,WS2812B,WS2812B,14,
14,"5.2 x 5.2mm Push Button, SMT",SW_Push,SW1,5.2x5.2mm,SKQG-1155865,1,
15,ATmega32U4-MU,ATmega32U4-MU-MCU_Microchip_ATmega,U1,ATmega32U4-MU,QFN-44-1EP_7x7mm_Pitch0.5mm,1,http://ww1.microchip.com/downloads/en/DeviceDoc/Atmel-7766-8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
16,ESD Protection IC,PRTR5V0U2X,U2,PRTR5V0U2X,SOT143B,1,
17,USB Type-C Connector,HRO-TYPE-C-31-M-12,USB1,HRO-TYPE-C-31-M-12,HRO-TYPE-C-31-M-12-Assembly,1,
18,"Crystal, 3.2 x 2.5mm, 16MHz",Crystal_GND24,Y1,16Mhz,Crystal_SMD_3225-4pin_3.2x2.5mm,1,
